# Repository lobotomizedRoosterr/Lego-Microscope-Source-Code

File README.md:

# LEGO Computational Microscope (ESP32-S3)

> **Status:** This repository is currently incomplete and is intended for the LEGO Computational Microscope outreach project based on the ESP32-S3.

## Overview

This repository contains the source code for the LEGO Computational Microscope outreach project. It is designed to be used with **ESP-IDF v5.3.5** and the **VS Code ESP-IDF Extension**.

> **Note**
> Development has only been tested on **Windows**. macOS and Linux instructions are based on the official Espressif documentation.

---

# Prerequisites

Before getting started, install the prerequisites listed in the official Espressif documentation:

https://docs.espressif.com/projects/vscode-esp-idf-extension/en/latest/prerequisites.html

## Windows

Install:

- Git
- Python 3.10, 3.11, 3.12, 3.13, or 3.14

> **Note:** The ESP-IDF installer automatically installs any missing Windows dependencies.

---

## macOS
Instructions can also be found here https://docs.espressif.com/projects/esp-idf/en/v5.3.5/esp32s3/get-started/linux-macos-setup.html

Install:

- git
- Homebrew
- Ninja
- CMake
- dfu-util
- Python (with pip, virtual environment support, and SSL support)

---

## Linux

Install:

- git
- CMake
- wget
- flex
- bison
- gperf
- ccache
- libffi-dev
- libssl-dev
- dfu-util
- libusb-1.0-0
- Python (with pip, virtual environment support, and SSL support)

---

# Installation

## Step 1 — Install the ESP-IDF Extension

1. Open **Visual Studio Code**.
2. Install the **ESP-IDF** extension from the Extensions Marketplace.
3. Verify that the extension is enabled.

---

## Step 2 — Install ESP-IDF

Open the Command Palette:

```
View → Command Palette
```

Run:

```
ESP-IDF: Open ESP-IDF Installation Manager
```

Alternatively, download the ESP-IDF Installation Manager (EIM):

https://dl.espressif.com/dl/eim/index.html

Install:

- **ESP-IDF v5.3.5**

---

## Step 3 — Configure VS Code

The ESP-IDF extension normally detects installations automatically using the EIM configuration file.

Default locations:

### Windows

```
C:\Espressif\tools\eim_idf.json
```

### macOS / Linux

```
$HOME/.espressif/tools/eim_idf.json
```

If VS Code does not detect your installation:

1. Open **Preferences → Settings**.
2. Search for:

```
idf.eimIdfJsonPath
```

3. Set the path to your `eim_idf.json` file.

---

## Step 4 — Open the git repo on VS-Code

1. Open the command palette on VS-Code
2. Type the command "Git: Clone" and run it
4. Enter the URL for the repo https://github.com/Zangle-Lab/Lego-Microscope-Source-Code
5. Select "Clone from URL"
6. Select a directory to clone the project to

---

## Step 5 - Configure ESP-IDF Version

1. Go to command palette
2. Type "ESP-IDF: Select Current ESP-IDF Version"
3. Select v5.3.5

---

## Step 6 — Reconfigure the Project

Open the Command Palette and run:

```
ESP-IDF: Run idf.py reconfigure Task
```

Wait for the process to complete.

---

## Step 7 — Build the Project

Build the project using either method:

### Option 1

Click the **Build** (wrench) icon in the VS Code status bar.

### Option 2

Run:

```
ESP-IDF: Build Your Project
```

The initial build may take several minutes.

A successful build should produce the project binaries without errors.

---

## Step 8 — Configure the Serial Port

Connect the ESP32-S3 to your computer.

> **Important:** Use a **USB data cable**. Many USB charging cables do **not** support data transfer.

Open the Command Palette:

```
ESP-IDF: Select Port to Use
```

The extension should detect the correct port automatically.

If it does not:

### Windows

1. Open **Device Manager**.
2. Expand **Ports (COM & LPT)**.
3. Locate your ESP32 device.
4. Select the corresponding COM port in VS Code.

If no device appears:

- Verify the USB cable supports data.
- Ensure the board is connected to the USB port used for programming.
- Try another USB cable or USB port.

---

## Step 10 — Flash and Monitor

Building the project **does not** automatically flash it.

Likewise, flashing **does not** rebuild any code changes.

Use UART as a flash method.

A typical development workflow is:

1. Build
2. Flash
3. Monitor

The monitor displays serial output from the ESP32-S3, making it useful for debugging.

---

# Notes

## Reconfiguring

Run:

```
ESP-IDF: Run idf.py reconfigure Task
```

whenever:

- files are added
- files are removed
- `sdkconfig` is modified

---

## Importance of sdkconfig

sdkconfig is vital for the project to run properly.

In general, the following must be configured (note that this is done in the repo's sdkconfig file)

- External PSRAM supported
- Octal SPI mode PSRAM
- External Flash Support
- Quad SPI Flash
- 16 mb Flash

---

# Repository Structure

```
.
├── components/
├── computation/
├── images/
├── main/
├── sdkconfig
├── CMakeLists.txt
└── README.md
```

---

# Troubleshooting

### VS Code cannot find ESP-IDF

- Verify ESP-IDF v5.3.5 is installed.
- Verify `eim_idf.json` exists.
- Check the `idf.eimIdfJsonPath` setting.

### ESP32 is not detected

- Use a USB **data** cable.
- Try another USB port.
- Check Device Manager for the COM port.

### Build errors after adding files

Run:

```
ESP-IDF: Run idf.py reconfigure Task
```

before rebuilding.

---

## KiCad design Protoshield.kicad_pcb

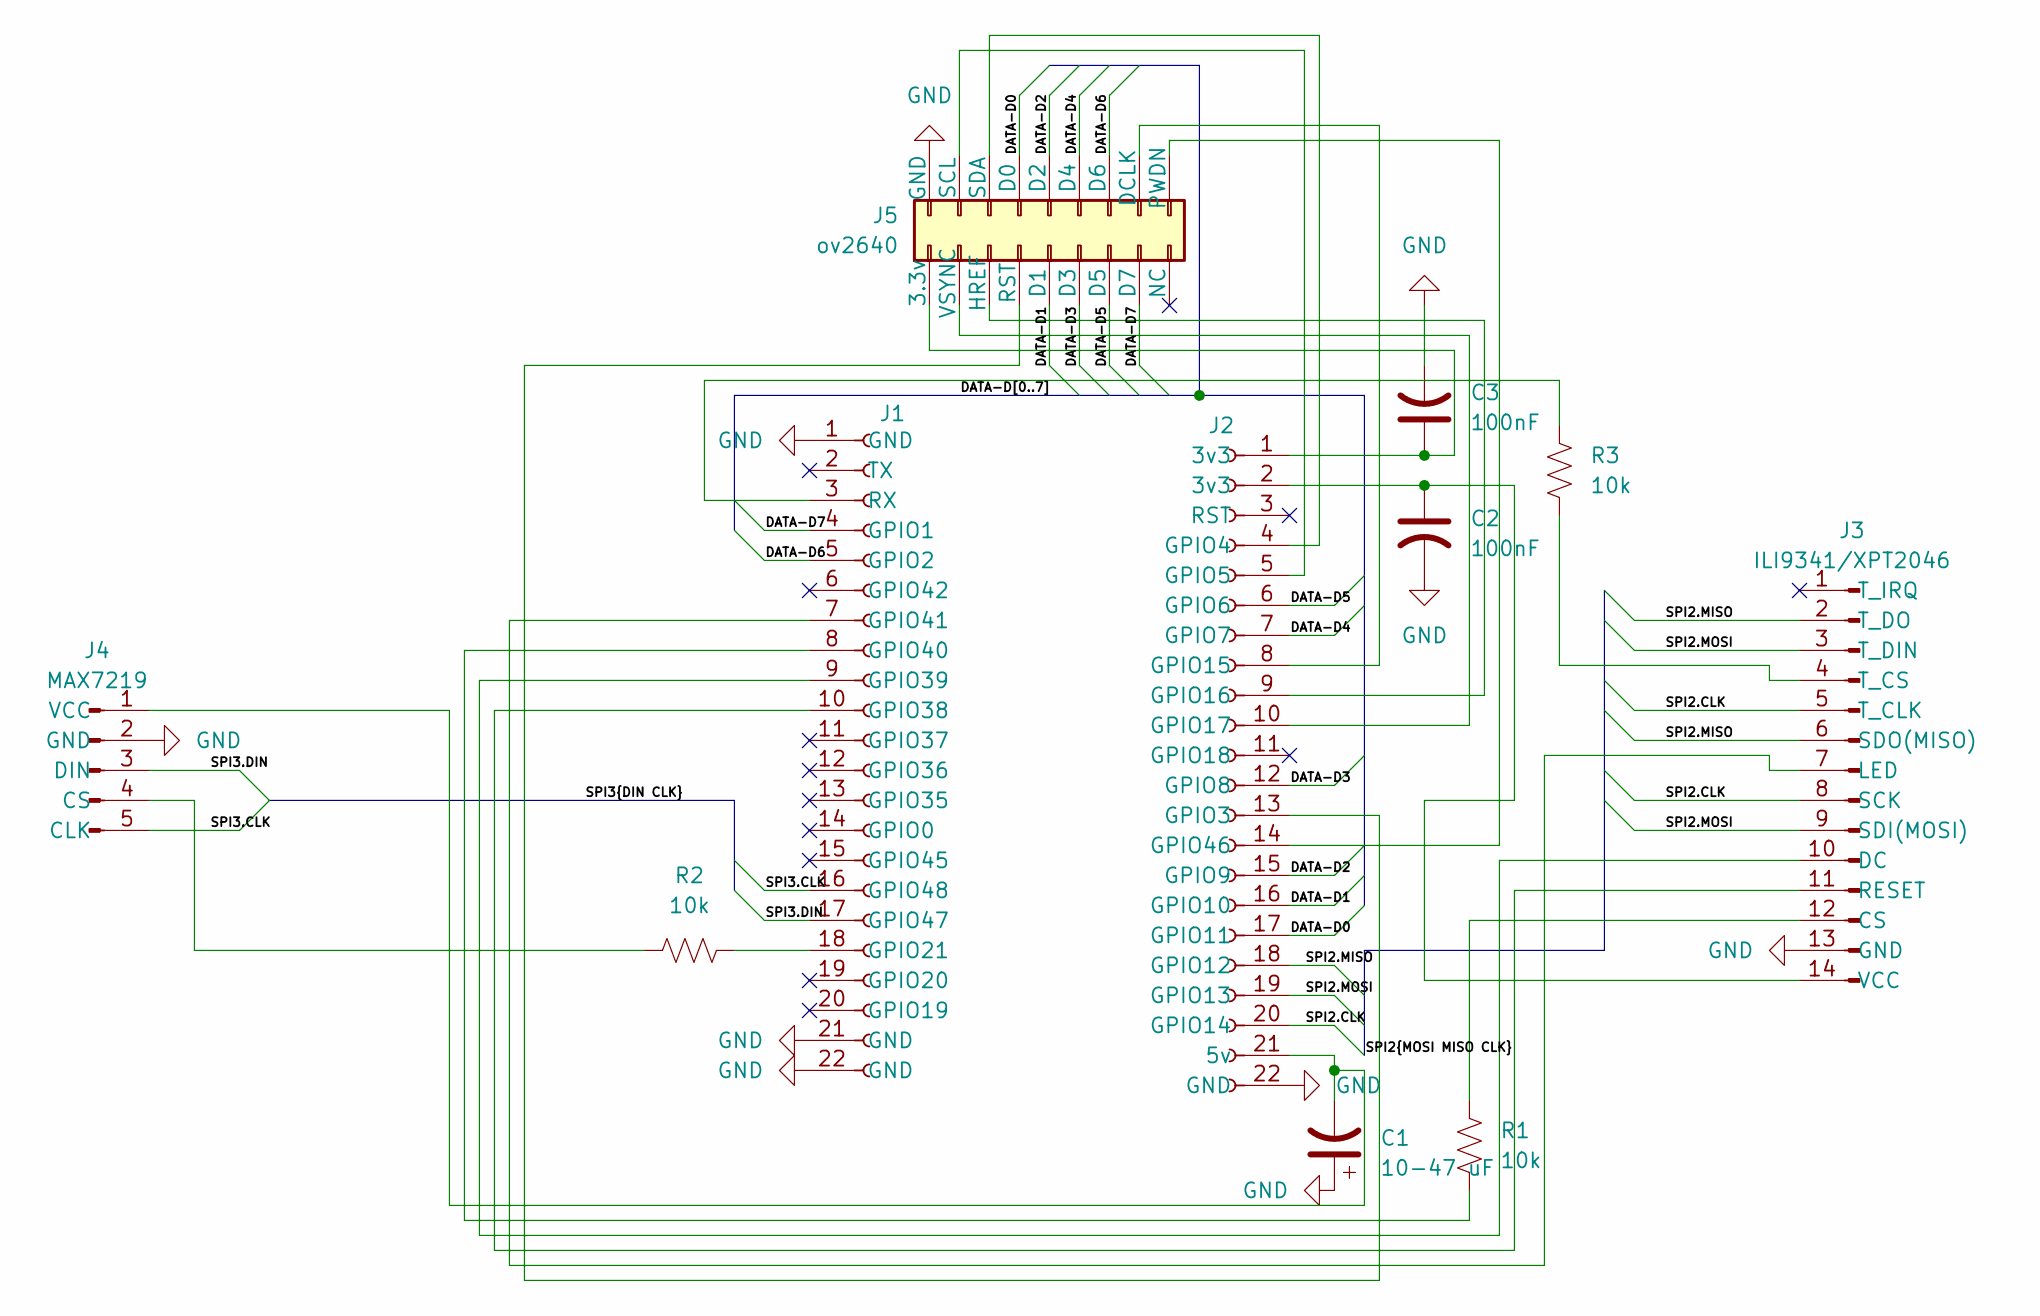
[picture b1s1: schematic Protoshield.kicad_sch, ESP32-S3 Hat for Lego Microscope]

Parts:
C1: 10-47 uF; CP_Radial_D6.3mm_P2.50mm
C2, C3: 100nF; C_Disc_D5.0mm_W2.5mm_P2.50mm
J1: ESP32-1; PinSocket_1x22_P2.54mm_Vertical
J2: ESP32-2; PinSocket_1x22_P2.54mm_Vertical
J3: ILI9341/XPT2046; PinHeader_1x14_P2.54mm_Vertical
J4: MAX7219; PinHeader_1x05_P2.54mm_Vertical
J5: ov2640; PinHeader_2x09_P2.54mm_Vertical
R1, R2, R3: 10k; R_Axial_DIN0207_L6.3mm_D2.5mm_P7.62mm_Horizontal

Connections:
/DATA-D0: J2.17 (GPIO11), J5.8 (D0)
/DATA-D1: J2.16 (GPIO10), J5.9 (D1)
/DATA-D2: J2.15 (GPIO9), J5.10 (D2)
/DATA-D3: J2.12 (GPIO8), J5.11 (D3)
/DATA-D4: J2.7 (GPIO7), J5.12 (D4)
/DATA-D5: J2.6 (GPIO6), J5.13 (D5)
/DATA-D6: J1.5 (GPIO2), J5.14 (D6)
/DATA-D7: J1.4 (GPIO1), J5.15 (D7)
/SPI2.CLK: J2.20 (GPIO14), J3.5 (T_CLK), J3.8 (SCK)
/SPI2.MISO: J2.18 (GPIO12), J3.2 (T_DO), J3.6 (SDO(MISO))
/SPI2.MOSI: J2.19 (GPIO13), J3.3 (T_DIN), J3.9 (SDI(MOSI))
/SPI3.CLK: J1.16 (GPIO48), J4.5 (CLK)
/SPI3.DIN: J1.17 (GPIO47), J4.3 (DIN)
GND: C1.1, C2.2, C3.2, J1.1 (GND), J1.21 (GND), J1.22 (GND), J2.22 (GND), J3.13 (GND), J4.2 (GND), J5.2 (GND)
unnamed: J1.18 (GPIO21), R2.2
unnamed: J1.10 (GPIO38), J3.11 (RESET)
unnamed: J1.9 (GPIO39), J3.10 (DC)
unnamed: J1.8 (GPIO40), R1.2
unnamed: J1.7 (GPIO41), J3.7 (LED)
unnamed: J1.3 (RX), R3.1
unnamed: C1.2, J2.21 (5v), J4.1 (VCC)
unnamed: J2.13 (GPIO3), J5.7 (RST)
unnamed: J2.4 (GPIO4), J5.6 (SDA)
unnamed: J2.5 (GPIO5), J5.4 (SCL)
unnamed: J2.8 (GPIO15), J5.16 (DCLK)
unnamed: J2.9 (GPIO16), J5.5, J5.RST (HREF)
unnamed: J2.10 (GPIO17), J5.3 (VSYNC)
unnamed: J2.14 (GPIO46), J5.18 (PWDN)
unnamed: J3.12 (CS), R1.1
unnamed: J3.4 (T_CS), R3.2
unnamed: C2.1, J2.2 (3v3), J3.14 (VCC)
unnamed: J4.4 (CS), R2.1
unnamed: C3.1, J2.1 (3v3), J5.1 (3.3v)

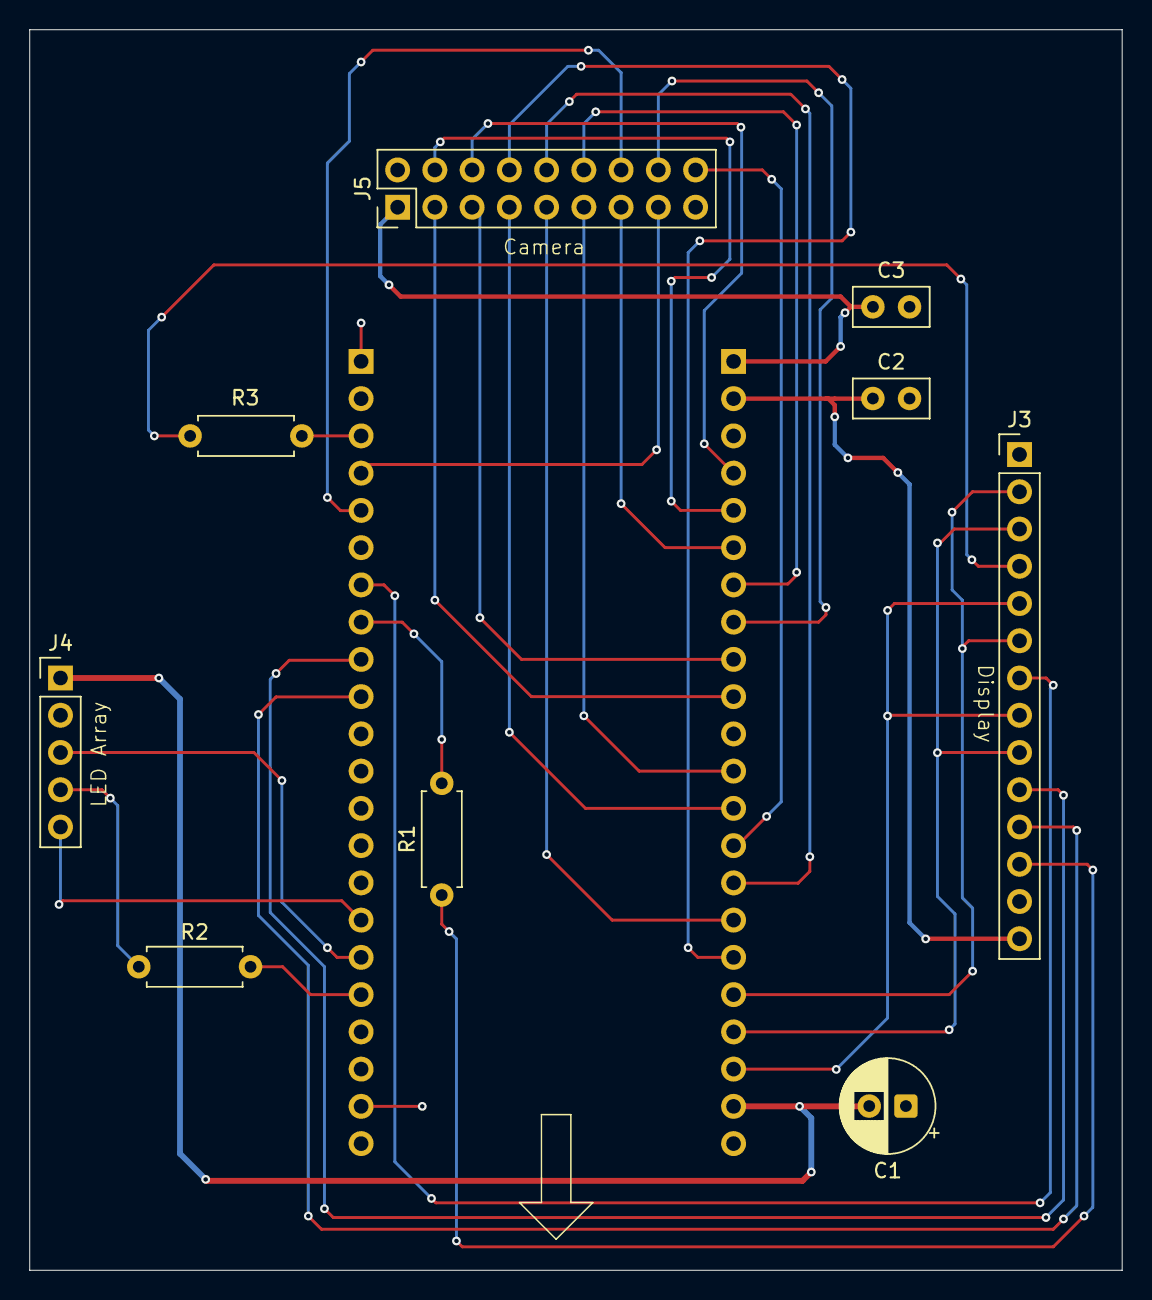
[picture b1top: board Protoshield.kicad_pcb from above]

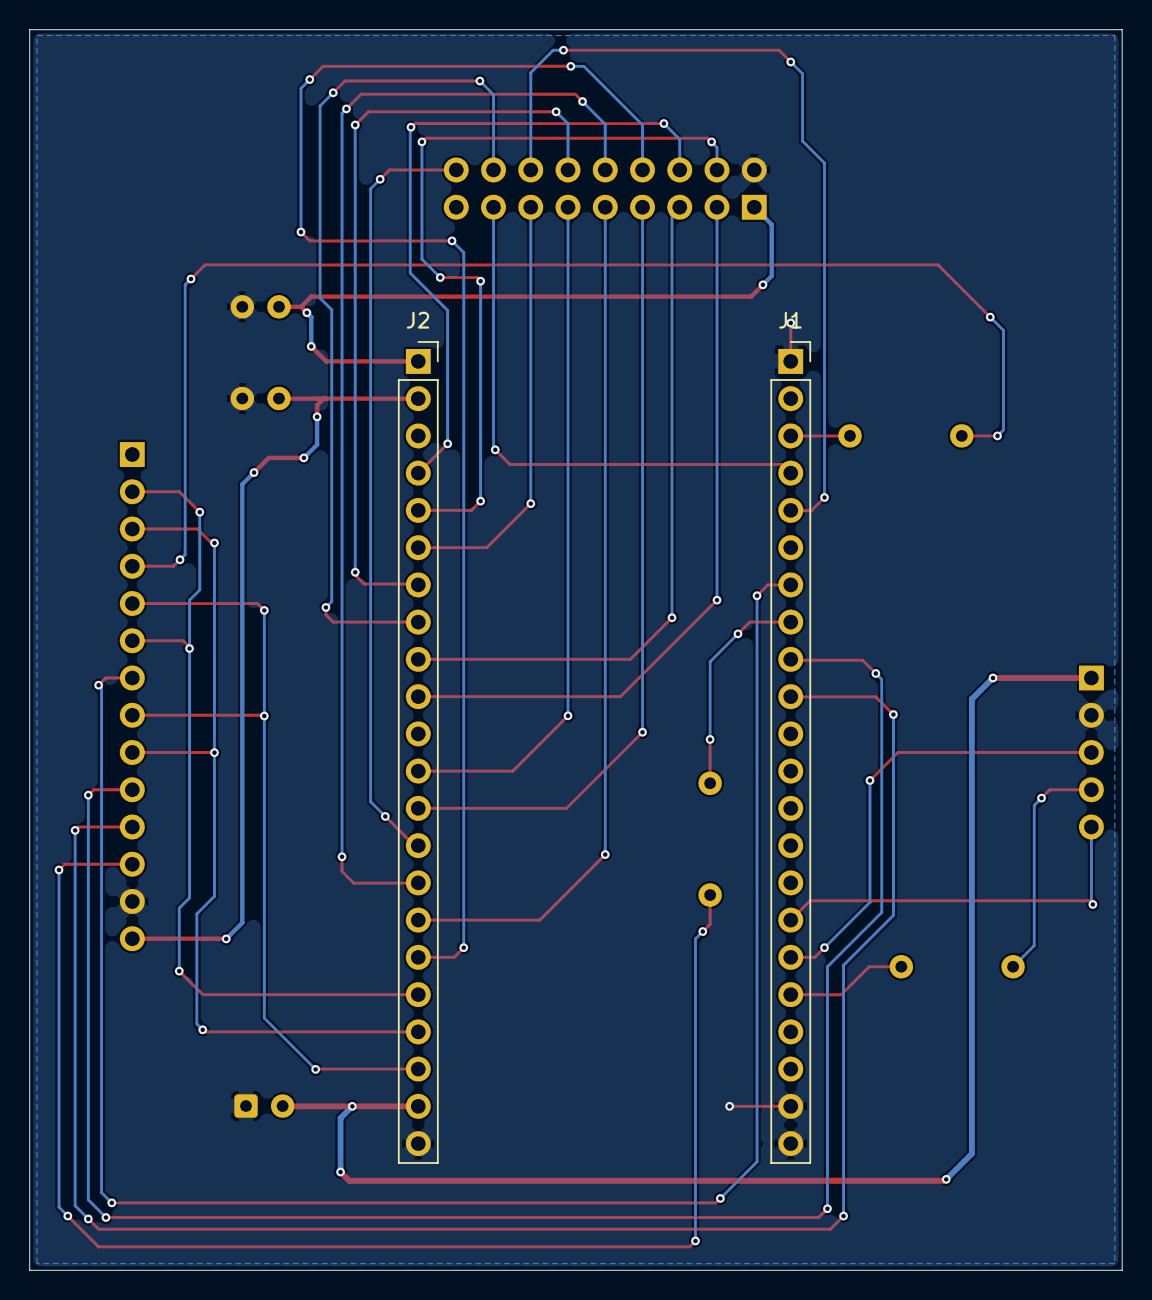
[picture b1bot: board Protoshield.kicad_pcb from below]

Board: 2 copper layers, 74.5 x 84.6 mm, 11 parts (2 on the bottom side), 33 nets.
